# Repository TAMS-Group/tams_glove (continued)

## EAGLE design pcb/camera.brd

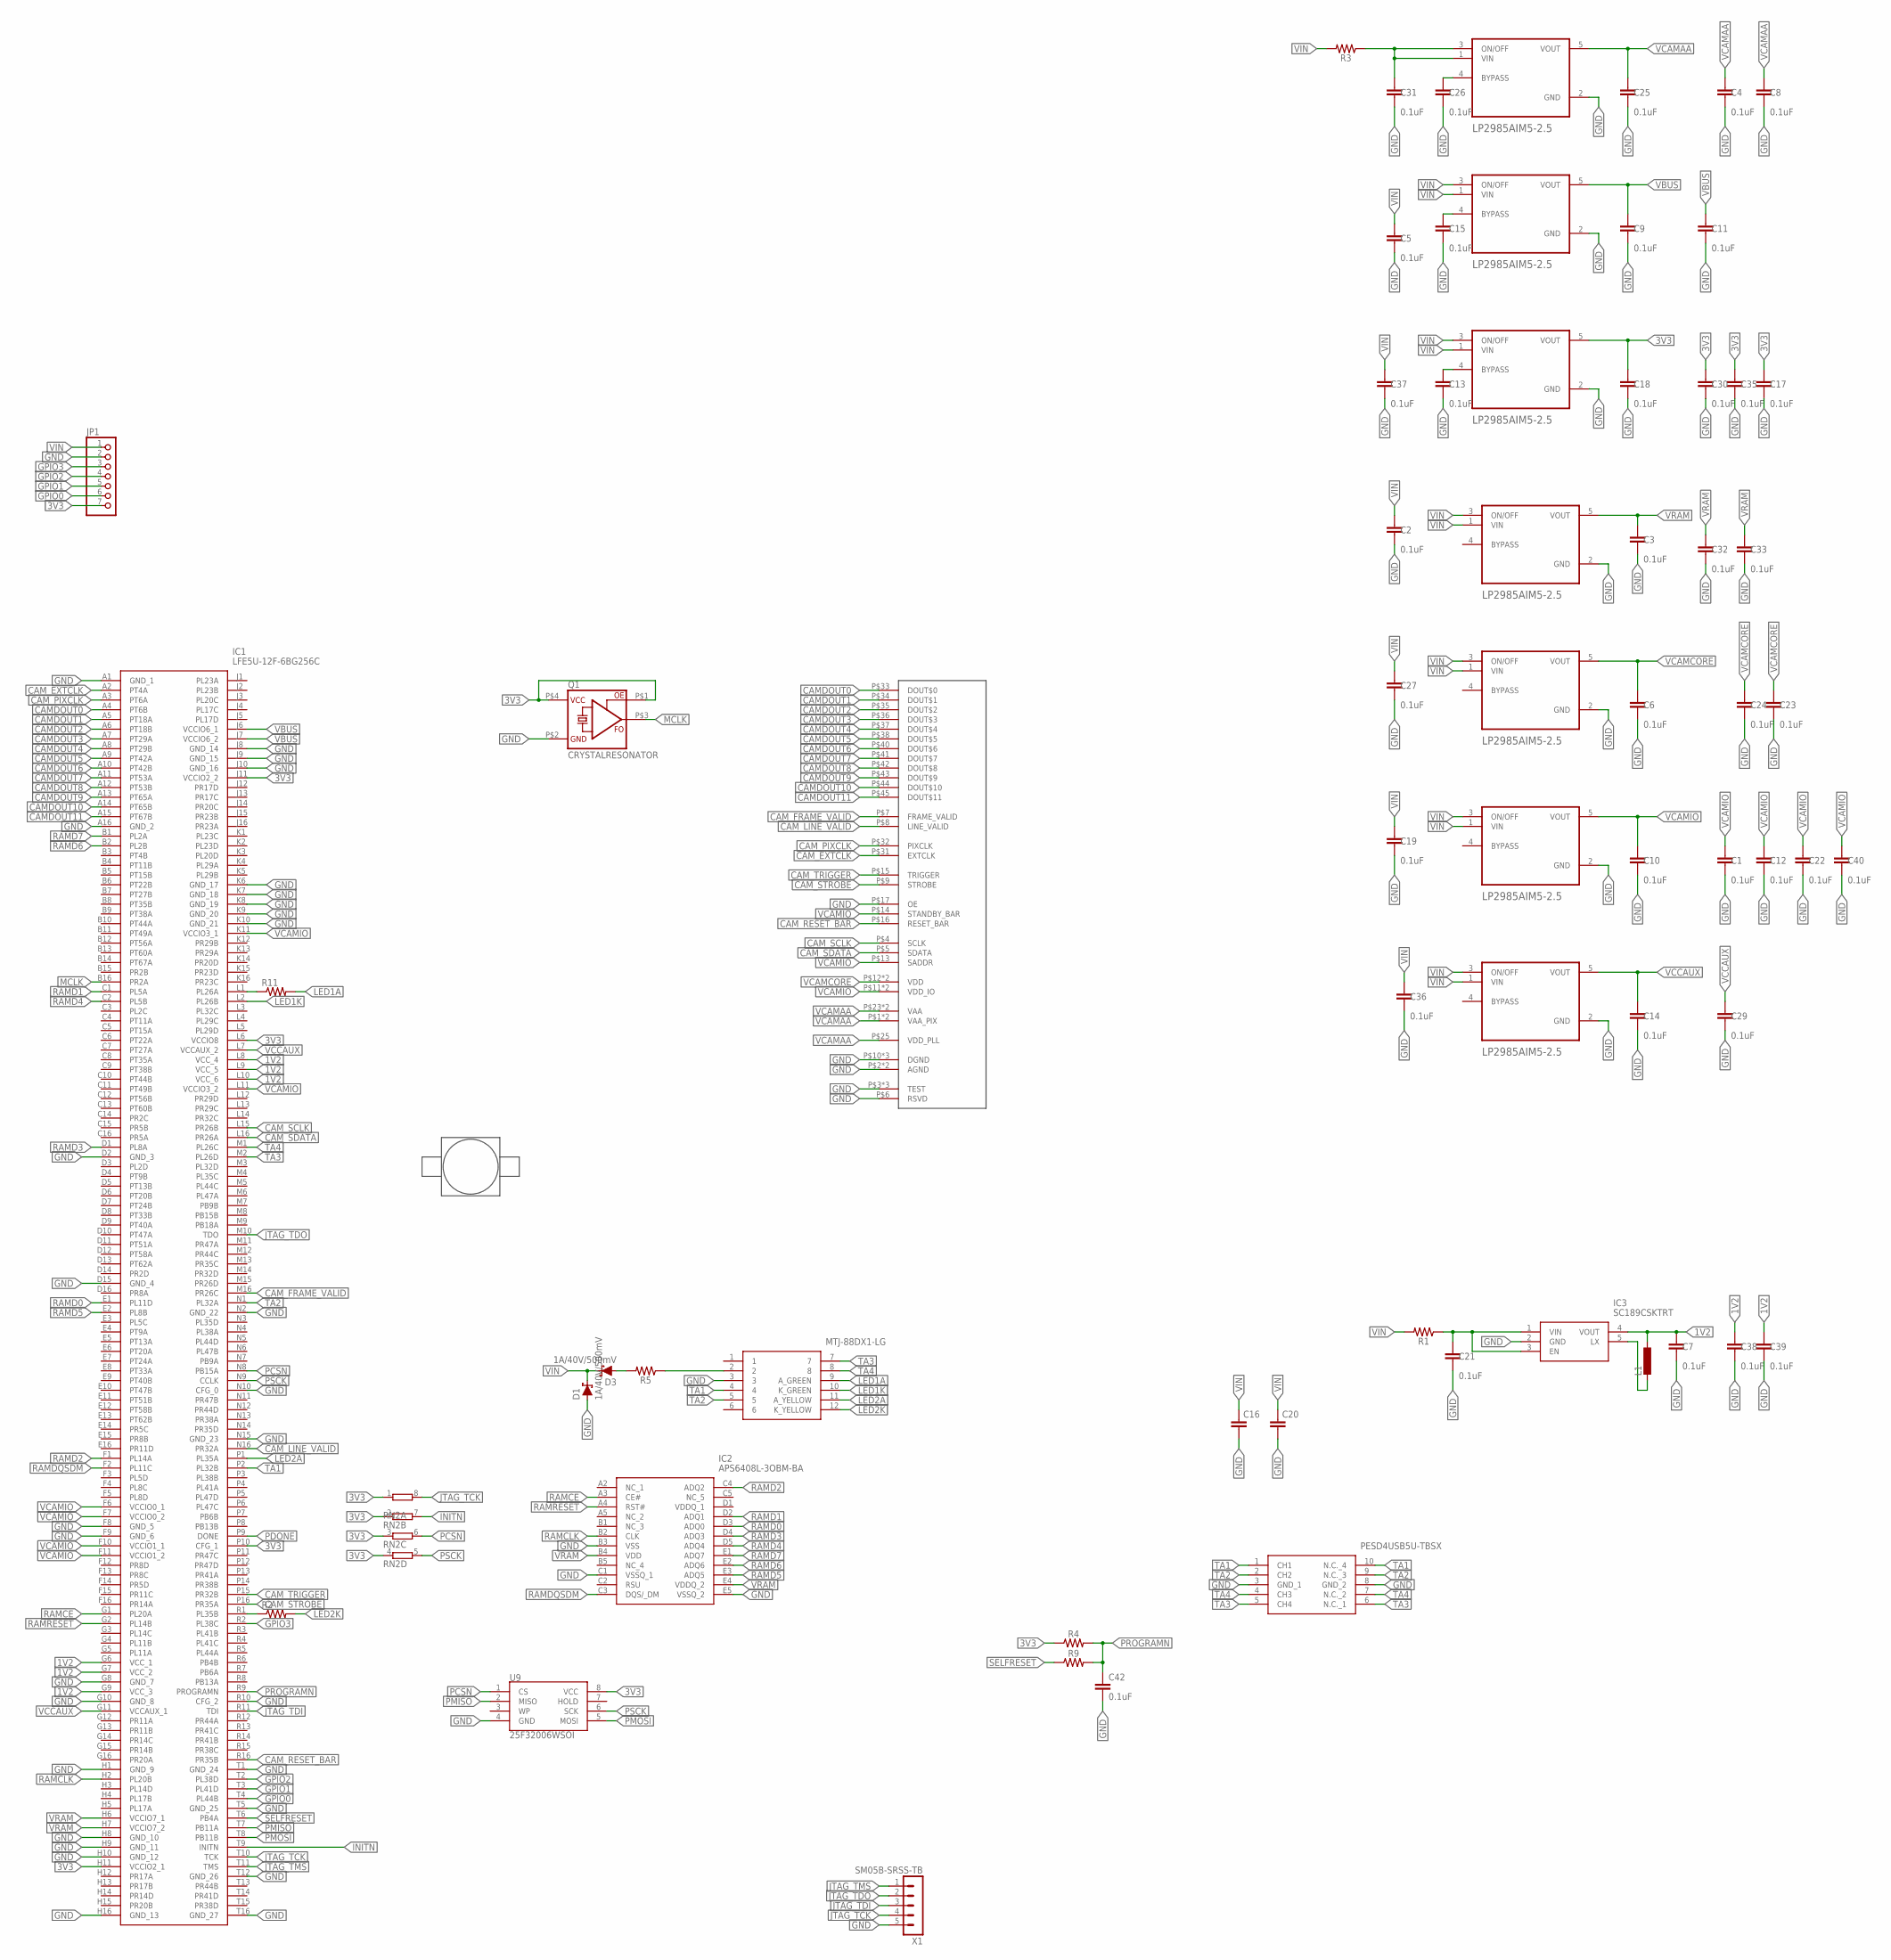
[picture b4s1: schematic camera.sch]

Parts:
C1, C2, C3, C4, C5, C6, C7, C8, C9, C10, C11, C12, C13, C14, C15, C17, C18, C19, C21, C22, C23, C24, C25, C26, C27, C29, C30, C31, C32, C33, C35, C36, C37, C38, C39, C40, C42: 0.1uF; 0603
C16, C20: C-EUC1812; C1812
D1, D3: 1A/40V/500mV; SMA-DIODE
D10: PESD4USB5U-TBSX; SON50P100X250X80-10N
IC1: LFE5U-12F-6BG256C; BGA256C80P16X16_1400X1400X170
IC2: APS6408L-3OBM-BA; BGA24C100P5X5_600X800X120
IC3: SC189CSKTRT; SOT95P280X145-5N
J1: MTJ-88DX1-LG; MTJ88DX1LG
JP1: PINHD-1X7M; 1X07M
L1: L-EUL3230M; L3230M
Q1: CRYSTALRESONATOR; XO53X
R1, R2, R3, R4, R9, R11: 0603
R5: 0805
RN2: 4R-NEXBV8V; EXBV8V
U1, U2, U3, U4, U5, U6, U8: LP2985AIM5-2.5; SOT95P280X145-5N
U9: 25F32006WSOI; SO08-EIAJ
U$1: LENS-HOLDER
U$2: MT9P001
X1: SM05B-SRSS-TB

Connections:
1V2: C7.1, C38.1, C39.1, IC1.G6 (VCC_1), IC1.G7 (VCC_2), IC1.G9 (VCC_3), IC1.L8 (VCC_4), IC1.L9 (VCC_5), IC1.L10 (VCC_6), IC3.4 (VOUT), L1.1
3V3: C17.1, C18.1, C30.1, C35.1, IC1.H11 (VCCIO2_1), IC1.J11 (VCCIO2_2), IC1.L6 (VCCIO8), IC1.P10 (CFG_1), JP1.7, Q1.P$1 (OE), Q1.P$4 (VCC), R4.1, RN2.1, RN2.2 (1), RN2.3 (1), RN2.4 (1), U2.5 (VOUT), U9.8 (VCC)
CAMDOUT0: IC1.A4 (PT6B), U$2.P$33 (DOUT$0)
CAMDOUT1: IC1.A5 (PT18A), U$2.P$34 (DOUT$1)
CAMDOUT2: IC1.A6 (PT18B), U$2.P$35 (DOUT$2)
CAMDOUT3: IC1.A7 (PT29A), U$2.P$36 (DOUT$3)
CAMDOUT4: IC1.A8 (PT29B), U$2.P$37 (DOUT$4)
CAMDOUT5: IC1.A9 (PT42A), U$2.P$38 (DOUT$5)
CAMDOUT6: IC1.A10 (PT42B), U$2.P$40 (DOUT$6)
CAMDOUT7: IC1.A11 (PT53A), U$2.P$41 (DOUT$7)
CAMDOUT8: IC1.A12 (PT53B), U$2.P$42 (DOUT$8)
CAMDOUT9: IC1.A13 (PT65A), U$2.P$43 (DOUT$9)
CAMDOUT10: IC1.A14 (PT65B), U$2.P$44 (DOUT$10)
CAMDOUT11: IC1.A15 (PT67B), U$2.P$45 (DOUT$11)
CAM_EXTCLK: IC1.A2 (PT4A), U$2.P$31 (EXTCLK)
CAM_FRAME_VALID: IC1.M16 (PR26C), U$2.P$7 (FRAME_VALID)
CAM_LINE_VALID: IC1.N16 (PR32A), U$2.P$8 (LINE_VALID)
CAM_PIXCLK: IC1.A3 (PT6A), U$2.P$32 (PIXCLK)
CAM_RESET_BAR: IC1.R16 (PR35B), U$2.P$16 (RESET_BAR)
CAM_SCLK: IC1.L15 (PR26B), U$2.P$4 (SCLK)
CAM_SDATA: IC1.L16 (PR26A), U$2.P$5 (SDATA)
CAM_STROBE: IC1.P16 (PR35A), U$2.P$9 (STROBE)
CAM_TRIGGER: IC1.P15 (PR32B), U$2.P$15 (TRIGGER)
GND: C1.2, C2.2, C3.2, C4.2, C5.2, C6.2, C7.2, C8.2, C9.2, C10.2, C11.2, C12.2, C13.2, C14.2, C15.2, C16.2, C17.2, C18.2, C19.2, C20.2, C21.2, C22.2, C23.2, C24.2, C25.2, C26.2, C27.2, C29.2, C30.2, C31.2, C32.2, C33.2, C35.2, C36.2, C37.2, C38.2, C39.2, C40.2, C42.2, D1.A, D10.3 (GND_1), D10.8 (GND_2), IC1.A1 (GND_1), IC1.A16 (GND_2), IC1.D2 (GND_3), IC1.D15 (GND_4), IC1.F8 (GND_5), IC1.F9 (GND_6), IC1.G8 (GND_7), IC1.G10 (GND_8), IC1.H1 (GND_9), IC1.H8 (GND_10), IC1.H9 (GND_11), IC1.H10 (GND_12), IC1.H16 (GND_13), IC1.J8 (GND_14), IC1.J9 (GND_15), IC1.J10 (GND_16), IC1.K6 (GND_17), IC1.K7 (GND_18), IC1.K8 (GND_19), IC1.K9 (GND_20), IC1.K10 (GND_21), IC1.N2 (GND_22), IC1.N10 (CFG_0), IC1.N15 (GND_23), IC1.R10 (CFG_2), IC1.T1 (GND_24), IC1.T5 (GND_25), IC1.T12 (GND_26), IC1.T16 (GND_27), IC2.B3 (VSS), IC2.C1 (VSSQ_1), IC2.E5 (VSSQ_2), IC3.2 (GND), J1.3, JP1.2, Q1.P$2 (GND), U1.2 (GND), U2.2 (GND), U3.2 (GND), U4.2 (GND), U5.2 (GND), U6.2 (GND), U8.2 (GND), U9.4 (GND), U$2.P$2 (AGND), U$2.P$3 (TEST), U$2.P$6 (RSVD), U$2.P$10 (DGND), U$2.P$17 (OE), U$2.P$20 (TEST), U$2.P$21 (TEST), U$2.P$22 (AGND), U$2.P$26 (DGND), U$2.P$46 (DGND), X1.5
GPIO0: IC1.T4 (PL44B), JP1.6
GPIO1: IC1.T3 (PL41D), JP1.5
GPIO2: IC1.T2 (PL38D), JP1.4
GPIO3: IC1.R2 (PL38C), JP1.3
INITN: IC1.T9 (INITN), RN2.7 (2)
JTAG_TCK: IC1.T10 (TCK), RN2.8 (2), X1.4
JTAG_TDI: IC1.R11 (TDI), X1.3
JTAG_TDO: IC1.M10 (TDO), X1.2
JTAG_TMS: IC1.T11 (TMS), X1.1
LED1A: J1.9 (A_GREEN), R11.2
LED1K: IC1.L2 (PL26B), J1.10 (K_GREEN)
LED2A: IC1.P1 (PL35A), J1.11 (A_YELLOW)
LED2K: J1.12 (K_YELLOW), R2.2
MCLK: IC1.B16 (PR2A), Q1.P$3 (FO)
unnamed: C15.1, U1.4 (BYPASS)
unnamed: C13.1, U2.4 (BYPASS)
unnamed: IC3.5 (LX), L1.2
unnamed: IC1.R1 (PL35B), R2.1
unnamed: C21.1, IC3.1 (VIN), IC3.3 (EN), R1.1
unnamed: C31.1, R3.1, U8.1 (VIN), U8.3 (ON/OFF)
unnamed: IC1.L1 (PL26A), R11.1
unnamed: J1.2, R5.1
unnamed: C26.1, U8.4 (BYPASS)
unnamed: D3.A, R5.2
PCSN: IC1.N8 (PB15A), RN2.6 (2), U9.1 (CS)
PDONE: IC1.P9 (DONE)
PMISO: IC1.T7 (PB11A), U9.2 (MISO)
PMOSI: IC1.T8 (PB11B), U9.5 (MOSI)
PROGRAMN: C42.1, IC1.R9 (PROGRAMN), R4.2, R9.2
PSCK: IC1.N9 (CCLK), RN2.5 (2), U9.6 (SCK)
RAMCE: IC1.G1 (PL20A), IC2.A3 (CE#)
RAMCLK: IC1.H2 (PL20B), IC2.B2 (CLK)
RAMD0: IC1.E1 (PL11D), IC2.D3 (ADQ0)
RAMD1: IC1.C1 (PL5A), IC2.D2 (ADQ1)
RAMD2: IC1.F1 (PL14A), IC2.C4 (ADQ2)
RAMD3: IC1.D1 (PL8A), IC2.D4 (ADQ3)
RAMD4: IC1.C2 (PL5B), IC2.D5 (ADQ4)
RAMD5: IC1.E2 (PL8B), IC2.E3 (ADQ5)
RAMD6: IC1.B2 (PL2B), IC2.E2 (ADQ6)
RAMD7: IC1.B1 (PL2A), IC2.E1 (ADQ7)
RAMDQSDM: IC1.F2 (PL11C), IC2.C3 (DQS/_DM)
RAMRESET: IC1.G2 (PL14B), IC2.A4 (RST#)
SELFRESET: IC1.T6 (PB4A), R9.1
TA1: D10.1 (CH1), D10.10 (N.C._4), IC1.P2 (PL32B), J1.4
TA2: D10.2 (CH2), D10.9 (N.C._3), IC1.N1 (PL32A), J1.5
TA3: D10.5 (CH4), D10.6 (N.C._1), IC1.M2 (PL26D), J1.7
TA4: D10.4 (CH3), D10.7 (N.C._2), IC1.M1 (PL26C), J1.8
VBUS: C9.1, C11.1, IC1.J6 (VCCIO6_1), IC1.J7 (VCCIO6_2), U1.5 (VOUT)
VCAMAA: C4.1, C8.1, C25.1, U8.5 (VOUT), U$2.P$1 (VAA_PIX), U$2.P$23 (VAA), U$2.P$24 (VAA), U$2.P$25 (VDD_PLL), U$2.P$48 (VAA_PIX)
VCAMCORE: C6.1, C23.1, C24.1, U4.5 (VOUT), U$2.P$12 (VDD), U$2.P$47 (VDD)
VCAMIO: C1.1, C10.1, C12.1, C22.1, C40.1, IC1.F6 (VCCIO0_1), IC1.F7 (VCCIO0_2), IC1.F10 (VCCIO1_1), IC1.F11 (VCCIO1_2), IC1.K11 (VCCIO3_1), IC1.L11 (VCCIO3_2), U5.5 (VOUT), U$2.P$11 (VDD_IO), U$2.P$13 (SADDR), U$2.P$14 (STANDBY_BAR), U$2.P$39 (VDD_IO)
VCCAUX: C14.1, C29.1, IC1.G11 (VCCAUX_1), IC1.L7 (VCCAUX_2), U6.5 (VOUT)
VIN: C2.1, C5.1, C16.1, C19.1, C20.1, C27.1, C36.1, C37.1, D1.C, D3.C, JP1.1, R1.2, R3.2, U1.1 (VIN), U1.3 (ON/OFF), U2.1 (VIN), U2.3 (ON/OFF), U3.1 (VIN), U3.3 (ON/OFF), U4.1 (VIN), U4.3 (ON/OFF), U5.1 (VIN), U5.3 (ON/OFF), U6.1 (VIN), U6.3 (ON/OFF)
VRAM: C3.1, C32.1, C33.1, IC1.H6 (VCCIO7_1), IC1.H7 (VCCIO7_2), IC2.B4 (VDD), IC2.E4 (VDDQ_2), U3.5 (VOUT)

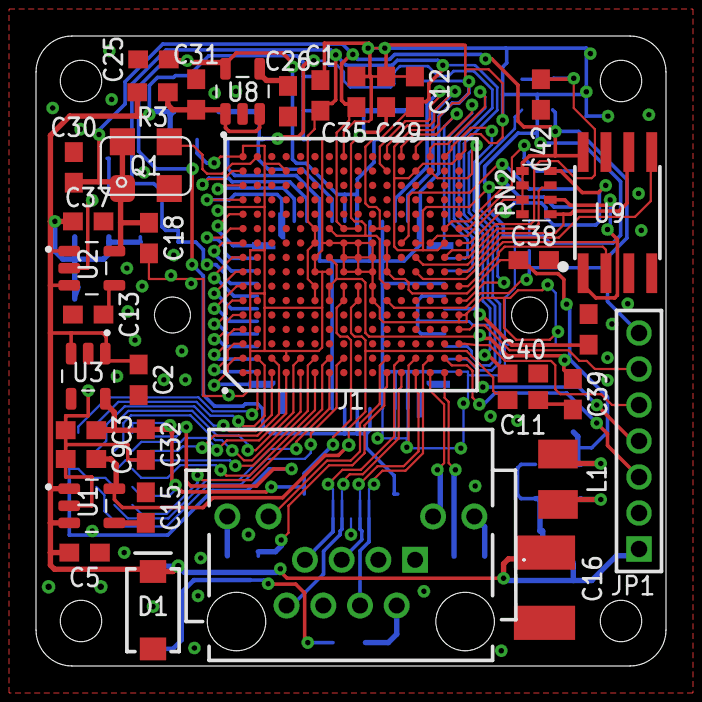
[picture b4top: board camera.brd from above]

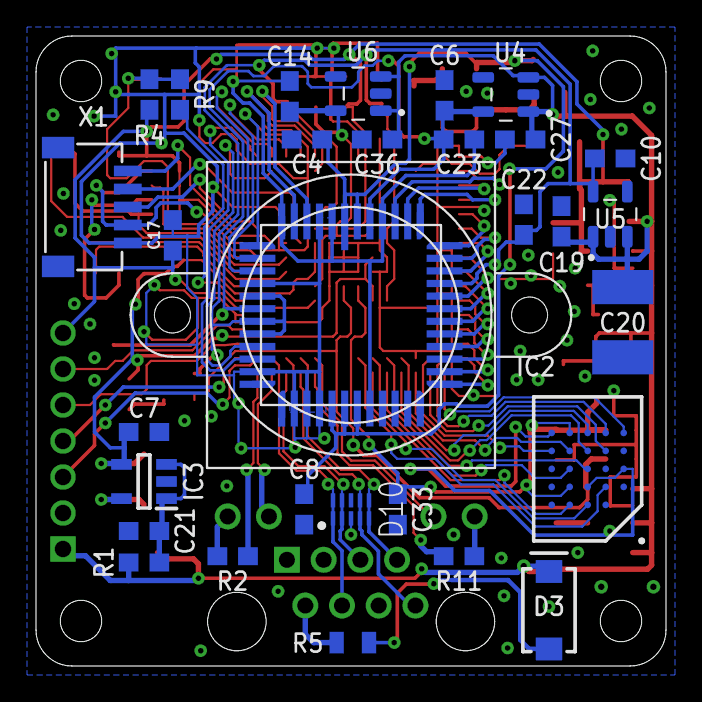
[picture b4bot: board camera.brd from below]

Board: 2 copper layers, 35.0 x 35.0 mm, 68 parts (31 on the bottom side), 77 nets.

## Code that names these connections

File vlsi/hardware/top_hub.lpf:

LOCATE COMP "mclk" SITE "K2";
LOCATE COMP "pin_clk" SITE "D8";
IOBUF PORT "pin_txen" IO_TYPE=LVCMOS33;
LOCATE COMP "pin_txen" SITE "F1";
IOBUF PORT "pin_txen" IO_TYPE=LVCMOS33 PULLMODE=UP DRIVE=4;
LOCATE COMP "pin_rxfn" SITE "G2";
IOBUF PORT "pin_rxfn" IO_TYPE=LVCMOS33 PULLMODE=UP DRIVE=4;
LOCATE COMP "pin_wrn" SITE "G1";
IOBUF PORT "pin_wrn" IO_TYPE=LVCMOS33 DRIVE=4;
LOCATE COMP "pin_rdn" SITE "J1";
IOBUF PORT "pin_rdn" IO_TYPE=LVCMOS33 DRIVE=4;
LOCATE COMP "pin_oen" SITE "K1";
IOBUF PORT "pin_oen" IO_TYPE=LVCMOS33 DRIVE=4;

LOCATE COMP "pin_net_clk[0]" SITE "L1"; LOCATE COMP "pin_net_dat[0]" SITE "M1";
LOCATE COMP "pin_net_clk[1]" SITE "N1"; LOCATE COMP "pin_net_dat[1]" SITE "P1";
LOCATE COMP "pin_net_clk[2]" SITE "R2"; LOCATE COMP "pin_net_dat[2]" SITE "R4";
LOCATE COMP "pin_net_clk[3]" SITE "P4"; LOCATE COMP "pin_net_dat[3]" SITE "R5";

LOCATE COMP "pin_net_clk[7]" SITE "R12"; LOCATE COMP "pin_net_dat[7]" SITE "R13";
LOCATE COMP "pin_net_clk[6]" SITE "R15"; LOCATE COMP "pin_net_dat[6]" SITE "P16";
LOCATE COMP "pin_net_clk[5]" SITE "N16"; LOCATE COMP "pin_net_dat[5]" SITE "L16";
LOCATE COMP "pin_net_clk[4]" SITE "J16"; LOCATE COMP "pin_net_dat[4]" SITE "G16";

LOCATE COMP "pin_ledctrl" SITE "B2";

LOCATE COMP "pin_be[0]" SITE "B1";
LOCATE COMP "pin_be[1]" SITE "C1";
LOCATE COMP "pin_be[2]" SITE "D1";
LOCATE COMP "pin_be[3]" SITE "E1";
LOCATE COMP "pin_data[0]" SITE "E13";
LOCATE COMP "pin_data[1]" SITE "D13";
LOCATE COMP "pin_data[2]" SITE "C13";
LOCATE COMP "pin_data[3]" SITE "A15";
LOCATE COMP "pin_data[4]" SITE "B14";
LOCATE COMP "pin_data[5]" SITE "A14";
LOCATE COMP "pin_data[6]" SITE "B13";
LOCATE COMP "pin_data[7]" SITE "A13";
LOCATE COMP "pin_data[8]" SITE "B12";
LOCATE COMP "pin_data[9]" SITE "A12";
LOCATE COMP "pin_data[10]" SITE "B11";
LOCATE COMP "pin_data[11]" SITE "A11";
LOCATE COMP "pin_data[12]" SITE "B10";
LOCATE COMP "pin_data[13]" SITE "A10";
LOCATE COMP "pin_data[14]" SITE "B9";
LOCATE COMP "pin_data[15]" SITE "A9";
LOCATE COMP "pin_data[16]" SITE "A8";
LOCATE COMP "pin_data[17]" SITE "B8";
LOCATE COMP "pin_data[18]" SITE "A7";
LOCATE COMP "pin_data[19]" SITE "B7";
LOCATE COMP "pin_data[20]" SITE "A6";
LOCATE COMP "pin_data[21]" SITE "B6";
LOCATE COMP "pin_data[22]" SITE "A5";
LOCATE COMP "pin_data[23]" SITE "B5";
LOCATE COMP "pin_data[24]" SITE "A4";
LOCATE COMP "pin_data[25]" SITE "B4";
LOCATE COMP "pin_data[26]" SITE "A3";
LOCATE COMP "pin_data[27]" SITE "B3";
LOCATE COMP "pin_data[28]" SITE "A2";
LOCATE COMP "pin_data[29]" SITE "C5";
LOCATE COMP "pin_data[30]" SITE "D4";
LOCATE COMP "pin_data[31]" SITE "E4";

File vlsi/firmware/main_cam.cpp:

// (c) 2021-2023 Philipp Ruppel

// #define SERIAL_UART

#include "gpio.hpp"
#include "messages.hpp"
#include "mt9p001.hpp"
#include "net.hpp"
#include "serial.hpp"
#include "thermometer.hpp"

#include <algorithm>
#include <array>
#include <cmath>
#include <cstring>

#define PIN_SCCB_SCL 0
#define PIN_SCCB_SDA 1
#define PIN_CAM_TRIGGER 2
#define PIN_CAM_RESET 3

#define PIN_LED1A 4
#define PIN_LED1K 5
#define PIN_LED2A 6
#define PIN_LED2K 7

#define g_ram_controller ((uint32_t *)(void *)0xB1000000)
#define g_ram_config ((uint32_t *)(void *)0xB2000000)
#define g_ram_data32 ((uint32_t *)(void *)0xB3000000)
#define g_ram_data8 ((uint8_t *)(void *)0xB3000000)

#define g_reg_pcam ((uint32_t *)0xB0000000)
#define g_reg_pcam_info_header_lower (g_reg_pcam[1])
#define g_reg_pcam_info_header_upper (g_reg_pcam[2])
#define g_reg_pcam_info_contents_lower (g_reg_pcam[3])
#define g_reg_pcam_info_contents_upper (g_reg_pcam[4])
#define g_reg_pcam_data_header (g_reg_pcam[5])
#define g_reg_pcam_enable_tx (g_reg_pcam[6])
#define g_reg_pcam_packet_count (g_reg_pcam[7])
#define g_reg_pcam_black_level (g_reg_pcam[8])

void main() {

  Serial.begin(1000000);

  pinMode(PIN_LED1A, OUTPUT);
  pinMode(PIN_LED1K, OUTPUT);
  pinMode(PIN_LED2A, OUTPUT);
  pinMode(PIN_LED2K, OUTPUT);

  digitalWrite(PIN_LED1A, 1);
  digitalWrite(PIN_LED1K, 0);
  digitalWrite(PIN_LED2A, 1);
  digitalWrite(PIN_LED2K, 0);

  delay(100);

  g_reg_net_phase_shift = 4;

  Serial.println("reset ram");
  g_ram_controller[0] = 0;
  delay(50);
  g_ram_controller[0] = 1;
  delay(50);

  Serial.println("ram reset done");

  Serial.println("config ram");
  // delay(100);
  // set drive strength
  // g_ram_config[0] = 0b00001010; // 1/4
  g_ram_config[0] = 0b00001001; // 1/2
  // g_ram_config[0] = 0b00001000; // full

  // g_ram_config[8] = 0; // burst

  // latency | slow refresh | no refresh
  g_ram_config[4] = 0b01001100;
  // g_ram_config[4] = 0b0000010;

  Serial.println("ram configured");

  pinMode(PIN_LED1A, OUTPUT);
  pinMode(PIN_LED1K, OUTPUT);
  pinMode(PIN_LED2A, OUTPUT);
  pinMode(PIN_LED2K, OUTPUT);

  digitalWrite(PIN_LED1A, 1);
  digitalWrite(PIN_LED1K, 0);
  digitalWrite(PIN_LED2A, 1);
  digitalWrite(PIN_LED2K, 0);

  delay(50);

  digitalWrite(PIN_LED1A, 0);
  digitalWrite(PIN_LED1K, 1);
  digitalWrite(PIN_LED2A, 0);
  digitalWrite(PIN_LED2K, 1);

  pinMode(PIN_CAM_RESET, OUTPUT); // reset
  digitalWrite(PIN_CAM_RESET, LOW);
  delay(50);
  digitalWrite(PIN_CAM_RESET, HIGH);
  delay(50);

  Serial.println("init camera");

  MT9P001 image_sensor(PIN_SCCB_SCL, PIN_SCCB_SDA);

  pinMode(PIN_CAM_TRIGGER, OUTPUT); // trigger
  digitalWrite(PIN_CAM_TRIGGER, HIGH);

  image_sensor.writeRegister(image_sensor.Read_Mode_1, // 256
                             (1 << 8)                  // snapshot
                                                       //||
                             //(1 << 9) // invert trigger
  );

  Serial.println("camera initialized");

  int frame_index = 0;

  bool led_flag = 0;

  delay(50);

  g_reg_pcam_data_header = 0xBA2FA166;

  g_reg_pcam_enable_tx = 1;

  bool event_pending = false;
  CameraMessage event_message;
  uint32_t event_time = 0;

  uint32_t temperature = 0;

  uint32_t last_width = -1;
  uint32_t last_height = -1;
  uint32_t last_shutter = -1;
  uint32_t last_addrmode = -1;

  uint16_t last_rgain = -1, last_ggain = -1, last_bgain = -1;

  ImageInfo info;

  NetworkPacketReceiver<8> receiver;
  while (true) {

    {
      uint32_t current_time = micros();
      if (receiver.receive()) {

        auto *packet = (const CameraMessage *)receiver.data();

        if (packet->magic == 0xCA62) {

          if (verify_message_checksum(*packet)) {

            event_pending = true;
            event_message = *packet;
            event_time = current_time;

            uint32_t skip = (packet->skip + 1);

            uint32_t left = packet->left;
            uint32_t top = packet->top;
            uint32_t width = packet->width;
            uint32_t height = packet->height;

            info = ImageInfo{0};
            info.magic = 0x8C53;
            info.width = width;
            info.height = height;
            info.left = left;
            info.top = top;
            info.temperature = (Thermometer.read() & 0b111111);
            info.skip = packet->skip;

            info.timestamp = packet->timestamp;
            update_message_checksum(info);

            Serial.print("verification time ");
            Serial.println(micros() - current_time);
          }
        }
      }
    }

    {
      uint32_t current_time = micros();
      if (event_pending && current_time - event_time >= event_message.delay) {

        event_pending = false;
        auto *packet = &event_message;

        uint32_t skip = (packet->skip + 1);

        uint32_t left = packet->left;
        uint32_t top = packet->top;
        uint32_t width = packet->width;
        uint32_t height = packet->height;

        uint32_t width_skip = width / skip;
        uint32_t height_skip = height / skip;

        image_sensor.writeRegister(image_sensor.Column_Start, left);
        image_sensor.writeRegister(image_sensor.Row_Start, top);

        if (width != last_width) {
          last_width = width;
          image_sensor.writeRegister(image_sensor.Column_Size, width - 1);
        }

        if (height != last_height) {
          last_height = height;
          image_sensor.writeRegister(image_sensor.Row_Size, height - 1);
        }

        uint16_t higain =
            (packet->digital_gain << 8) | (packet->double_gain << 6);

        uint16_t rgain = (higain | packet->analog_gain_red);
        uint16_t ggain = (higain | packet->analog_gain_green);
        uint16_t bgain = (higain | packet->analog_gain_blue);

        if (rgain != last_rgain) {
          last_rgain = rgain;
          image_sensor.writeRegister(image_sensor.Red_Gain, rgain);
        }

        if (ggain != last_ggain) {
          last_ggain = ggain;
          image_sensor.writeRegister(image_sensor.Green1_Gain, ggain);
          image_sensor.writeRegister(image_sensor.Green2_Gain, ggain);
        }

        if (bgain != last_bgain) {
          last_bgain = bgain;
          image_sensor.writeRegister(image_sensor.Blue_Gain, bgain);
        }

        if (packet->shutter != last_shutter) {
          last_shutter = packet->shutter;
          image_sensor.writeRegister(image_sensor.Shutter_Width_Lower,
                                     packet->shutter);
        }

        {
          uint32_t addrmode = (packet->skip | (packet->binning << 4));
          if (addrmode != last_addrmode) {
            last_addrmode = addrmode;
            image_sensor.writeRegister(image_sensor.Column_Address_Mode,
                                       addrmode);
            image_sensor.writeRegister(image_sensor.Row_Address_Mode, addrmode);
          }
        }

        g_reg_pcam_info_header_upper = info.v32[0];
        g_reg_pcam_info_header_lower = info.v32[1];
        g_reg_pcam_info_contents_upper = info.v32[2];
        g_reg_pcam_info_contents_lower = info.v32[3];

        g_reg_pcam_packet_count =
            1 + ((uint32_t(width_skip) * uint32_t(height_skip) + 63) / 64);
        g_reg_pcam_black_level = packet->blacklevel;

        digitalWrite(PIN_CAM_TRIGGER, LOW);
        digitalWrite(PIN_CAM_TRIGGER, HIGH);

        led_flag = !led_flag;
        if (led_flag) {
          digitalWrite(PIN_LED1A, 0);
          digitalWrite(PIN_LED1K, 1);
          digitalWrite(PIN_LED2A, 1);
          digitalWrite(PIN_LED2K, 0);
        } else {
          digitalWrite(PIN_LED1A, 1);
          digitalWrite(PIN_LED1K, 0);
          digitalWrite(PIN_LED2A, 0);
          digitalWrite(PIN_LED2K, 1);
        }

        uint32_t ready_time = micros();

        Serial.print("trigger ");
        Serial.print(current_time - event_time);
        Serial.print(" ");
        Serial.print(ready_time - event_time);
        Serial.println();

        temperature = Thermometer.read();
      }
    }
  }
}
